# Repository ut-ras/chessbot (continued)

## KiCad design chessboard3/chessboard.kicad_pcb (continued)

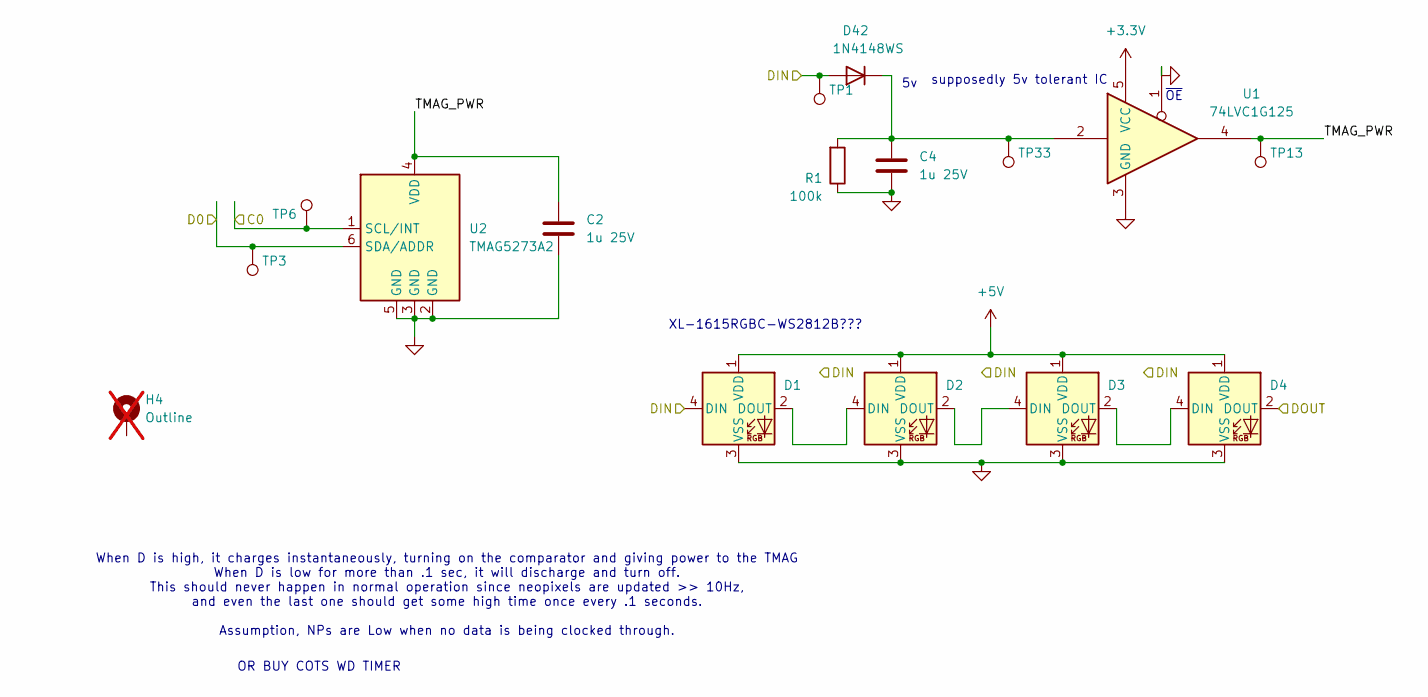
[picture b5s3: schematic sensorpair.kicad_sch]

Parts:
C2: 1u 25V; C_0402_1005Metric_Pad0.74x0.62mm_HandSolder
C4: 1u 25V; C_0402_1005Metric
D1, D2, D3, D4: XL-2121RGBC-WS2812B; SK6812-MINI-E-no-cut
D42: 1N4148WS; D_SOD-323_HandSoldering
H4: Outline; outline; not fitted
R1: 100k; R_0402_1005Metric_Pad0.72x0.64mm_HandSolder
TP1, TP3, TP6, TP13, TP33: TestPoint; TestPoint_THTPad_D1.0mm_Drill0.5mm
U1: 74LVC1G125; SOT-353_SC-70-5
U2: TMAG5273A2; SOT-23-6; LCSC C3715882

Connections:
+3.3V: U1.5 (VCC); also elsewhere on the board
+5V: D1.1 (VDD), D2.1 (VDD), D3.1 (VDD), D4.1 (VDD); also elsewhere on the board
/LED_IN: D1.4 (DIN), D42.2 (A), TP1.1; also elsewhere on the board
/Row0/sensorpair0/DOUT: D4.2 (DOUT); also elsewhere on the board
/Row0/sensorpair0/TMAG_PWR: C2.1, TP13.1, U1.4, U2.4 (VDD)
/SCL: TP6.1, U2.1 (SCL/INT); also elsewhere on the board
/SDA: TP3.1, U2.6 (SDA/ADDR); also elsewhere on the board
GND: C2.2, C4.2, D1.3 (VSS), D2.3 (VSS), D3.3 (VSS), D4.3 (VSS), R1.1, U1.1, U1.3 (GND), U2.2 (GND), U2.3 (GND), U2.5 (GND); also elsewhere on the board
unnamed: D1.2 (DOUT), D2.4 (DIN)
unnamed: D2.2 (DOUT), D3.4 (DIN)
unnamed: D3.2 (DOUT), D4.4 (DIN)
unnamed: C4.1, D42.1 (K), R1.2, TP33.1, U1.2

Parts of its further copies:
C6, C9, C11, C13, C15, C17, C19: 1u 25V; C_0402_1005Metric_Pad0.74x0.62mm_HandSolder
C7, C8, C10, C12, C14, C16, C18: 1u 25V; C_0402_1005Metric
D5, D6, D7, D8, D9, D10, D11, D12, D13, D14, D15, D16, D17, D18, D19, D20, D21, D22, D23, D24, D25, D26, D27, D28, D29, D30, D31, D32: XL-2121RGBC-WS2812B; SK6812-MINI-E-no-cut
D45, D48, D51, D54, D57, D60, D63: 1N4148WS; D_SOD-323_HandSoldering
H5, H6, H7, H8, H9, H10, H11: Outline; outline; not fitted
R9, R15, R21, R35, R37, R39, R41: 100k; R_0402_1005Metric_Pad0.72x0.64mm_HandSolder
TP2, TP4, TP5, TP7, TP8, TP9, TP10, TP11, TP12, TP14, TP15, TP16, TP17, TP18, TP19, TP20, TP21, TP22, TP23, TP24, TP25, TP26, TP27, TP28, TP29, TP30, TP31, TP32, TP34, TP35, TP36, TP37, TP38, TP39, TP40: TestPoint; TestPoint_THTPad_D1.0mm_Drill0.5mm
U3, U5, U7, U9, U13, U15, U17: TMAG5273A2; SOT-23-6; LCSC C3715882
U4, U6, U8, U11, U12, U14, U16: 74LVC1G125; SOT-353_SC-70-5

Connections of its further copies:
+3.3V: U4.5 (VCC), U6.5 (VCC), U8.5 (VCC), U11.5 (VCC), U12.5 (VCC), U14.5 (VCC), U16.5 (VCC); also elsewhere on the board
+5V: D5.1 (VDD), D6.1 (VDD), D7.1 (VDD), D8.1 (VDD), D9.1 (VDD), D10.1 (VDD), D11.1 (VDD), D12.1 (VDD), D13.1 (VDD), D14.1 (VDD), D15.1 (VDD), D16.1 (VDD), D17.1 (VDD), D18.1 (VDD), D19.1 (VDD), D20.1 (VDD), D21.1 (VDD), D22.1 (VDD), D23.1 (VDD), D24.1 (VDD), D25.1 (VDD), D26.1 (VDD), D27.1 (VDD), D28.1 (VDD), D29.1 (VDD), D30.1 (VDD), D31.1 (VDD), D32.1 (VDD); also elsewhere on the board
/LED_OUT: D32.2 (DOUT); also elsewhere on the board
/Row0/sensorpair0/DOUT: D5.4 (DIN), D45.2 (A), TP2.1; also elsewhere on the board
/Row0/sensorpair1/DOUT: D8.2 (DOUT), D9.4 (DIN), D48.2 (A), TP4.1
/Row0/sensorpair1/TMAG_PWR: C6.1, TP14.1, U3.4 (VDD), U4.4
/Row0/sensorpair2/DOUT: D12.2 (DOUT), D13.4 (DIN), D51.2 (A), TP5.1
/Row0/sensorpair2/TMAG_PWR: C9.1, TP16.1, U5.4 (VDD), U6.4
/Row0/sensorpair3/DOUT: D16.2 (DOUT), D17.4 (DIN), D54.2 (A), TP7.1
/Row0/sensorpair3/TMAG_PWR: C11.1, TP17.1, U7.4 (VDD), U8.4
/Row0/sensorpair4/DOUT: D20.2 (DOUT), D21.4 (DIN), D57.2 (A), TP8.1
/Row0/sensorpair4/TMAG_PWR: C13.1, TP19.1, U9.4 (VDD), U11.4
/Row0/sensorpair5/DOUT: D24.2 (DOUT), D25.4 (DIN), D60.2 (A), TP10.1
/Row0/sensorpair5/TMAG_PWR: C15.1, TP20.1, U12.4, U13.4 (VDD)
/Row0/sensorpair6/DOUT: D28.2 (DOUT), D29.4 (DIN), D63.2 (A), TP11.1
/Row0/sensorpair6/TMAG_PWR: C17.1, TP22.1, U14.4, U15.4 (VDD)
/Row0/sensorpair7/TMAG_PWR: C19.1, TP23.1, U16.4, U17.4 (VDD)
/SCL: TP12.1, TP18.1, TP24.1, TP26.1, TP28.1, TP30.1, TP32.1, U3.1 (SCL/INT), U5.1 (SCL/INT), U7.1 (SCL/INT), U9.1 (SCL/INT), U13.1 (SCL/INT), U15.1 (SCL/INT), U17.1 (SCL/INT); also elsewhere on the board
/SDA: TP9.1, TP15.1, TP21.1, TP25.1, TP27.1, TP29.1, TP31.1, U3.6 (SDA/ADDR), U5.6 (SDA/ADDR), U7.6 (SDA/ADDR), U9.6 (SDA/ADDR), U13.6 (SDA/ADDR), U15.6 (SDA/ADDR), U17.6 (SDA/ADDR); also elsewhere on the board
GND: C6.2, C7.2, C8.2, C9.2, C10.2, C11.2, C12.2, C13.2, C14.2, C15.2, C16.2, C17.2, C18.2, C19.2, D5.3 (VSS), D6.3 (VSS), D7.3 (VSS), D8.3 (VSS), D9.3 (VSS), D10.3 (VSS), D11.3 (VSS), D12.3 (VSS), D13.3 (VSS), D14.3 (VSS), D15.3 (VSS), D16.3 (VSS), D17.3 (VSS), D18.3 (VSS), D19.3 (VSS), D20.3 (VSS), D21.3 (VSS), D22.3 (VSS), D23.3 (VSS), D24.3 (VSS), D25.3 (VSS), D26.3 (VSS), D27.3 (VSS), D28.3 (VSS), D29.3 (VSS), D30.3 (VSS), D31.3 (VSS), D32.3 (VSS), R9.1, R15.1, R21.1, R35.1, R37.1, R39.1, R41.1, U3.2 (GND), U3.3 (GND), U3.5 (GND), U4.1, U4.3 (GND), U5.2 (GND), U5.3 (GND), U5.5 (GND), U6.1, U6.3 (GND), U7.2 (GND), U7.3 (GND), U7.5 (GND), U8.1, U8.3 (GND), U9.2 (GND), U9.3 (GND), U9.5 (GND), U11.1, U11.3 (GND), U12.1, U12.3 (GND), U13.2 (GND), U13.3 (GND), U13.5 (GND), U14.1, U14.3 (GND), U15.2 (GND), U15.3 (GND), U15.5 (GND), U16.1, U16.3 (GND), U17.2 (GND), U17.3 (GND), U17.5 (GND); also elsewhere on the board
unnamed: D5.2 (DOUT), D6.4 (DIN)
unnamed: D6.2 (DOUT), D7.4 (DIN)
unnamed: D7.2 (DOUT), D8.4 (DIN)
unnamed: D9.2 (DOUT), D10.4 (DIN)
unnamed: D10.2 (DOUT), D11.4 (DIN)
unnamed: D11.2 (DOUT), D12.4 (DIN)
unnamed: D13.2 (DOUT), D14.4 (DIN)
unnamed: D14.2 (DOUT), D15.4 (DIN)
unnamed: D15.2 (DOUT), D16.4 (DIN)
unnamed: D17.2 (DOUT), D18.4 (DIN)
unnamed: D18.2 (DOUT), D19.4 (DIN)
unnamed: D19.2 (DOUT), D20.4 (DIN)
unnamed: D21.2 (DOUT), D22.4 (DIN)
unnamed: D22.2 (DOUT), D23.4 (DIN)
unnamed: D23.2 (DOUT), D24.4 (DIN)
unnamed: D25.2 (DOUT), D26.4 (DIN)
unnamed: D26.2 (DOUT), D27.4 (DIN)
unnamed: D27.2 (DOUT), D28.4 (DIN)
unnamed: D29.2 (DOUT), D30.4 (DIN)
unnamed: D30.2 (DOUT), D31.4 (DIN)
unnamed: D31.2 (DOUT), D32.4 (DIN)
unnamed: C7.1, D45.1 (K), R9.2, TP34.1, U4.2
unnamed: C8.1, D48.1 (K), R15.2, TP35.1, U6.2
unnamed: C10.1, D51.1 (K), R21.2, TP36.1, U8.2
unnamed: C12.1, D54.1 (K), R35.2, TP37.1, U11.2
unnamed: C14.1, D57.1 (K), R37.2, TP38.1, U12.2
unnamed: C16.1, D60.1 (K), R39.2, TP39.1, U14.2
unnamed: C18.1, D63.1 (K), R41.2, TP40.1, U16.2

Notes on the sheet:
XL-1615RGBC-WS2812B???
~{OE}
OR BUY COTS WD TIMER
When D is high, it charges instantaneously, turning on the comparator and giving power to the TMAG When D is low for more than .1 sec, it will discharge and turn off. This should never happen in normal operation since neopixels are updated >> 10Hz, and even the last one should get some high time on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
supposedly 5v tolerant IC

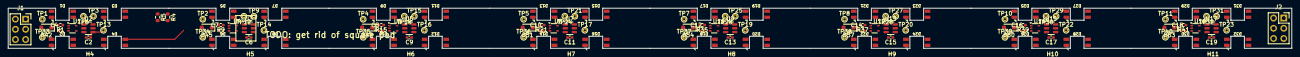
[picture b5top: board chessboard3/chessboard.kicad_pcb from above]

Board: 2 copper layers, 320.0 x 10.0 mm, 132 parts (0 on the bottom side), 54 nets.

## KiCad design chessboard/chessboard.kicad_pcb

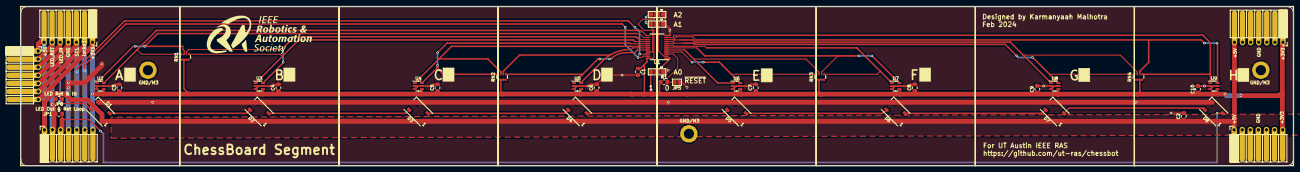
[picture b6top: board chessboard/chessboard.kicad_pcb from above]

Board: 2 copper layers, 400.0 x 50.0 mm, 46 parts (0 on the bottom side), 35 nets.

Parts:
C1, C3, C4, C5, C6, C7, C8, C9, C10: 100nF; C_0805_2012Metric_Pad1.18x1.45mm_HandSolder
C2: 22uF; C_0805_2012Metric_Pad1.18x1.45mm_HandSolder
D1, D2, D3, D4, D5, D6, D7, D8: XL-5050RGBC-WS2812B; LED_WS2812B_PLCC4_5.0x5.0mm_P3.2mm
H1, H2, H3: MountingHole_Pad; MountingHole_3.2mm_M3_ISO14580_Pad
J2, J3, J4, J5, J6: Conn_01x07; Custom PinSocket Edge Connector
JP1, JP6: SolderJumper_2_Open; R_0805_2012Metric_Pad1.20x1.40mm_HandSolder
JP2, JP3, JP4: SolderJumper_3_Open; SolderJumper-3_P2.0mm_Open_TrianglePad1.0x1.5mm
JP5: SolderJumper_2_Open; SolderJumper-2_P1.3mm_Open_Pad1.0x1.5mm
R1: 10k; R_0805_2012Metric_Pad1.20x1.40mm_HandSolder
RN1, RN2, RN3, RN4: 4.7k; R_Array_Convex_4x0603
U1: TCA9548APWR; TSSOP-24_4.4x7.8mm_P0.65mm
U2, U3, U4, U5, U6, U7, U8, U9: TMAG5273; SOT-23-6

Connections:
+3.3V: C1.1, C3.1, C4.1, C5.1, C6.1, C7.1, C8.1, C9.1, C10.1, J2.7, J3.1, J4.1, J5.7, J6.7, JP2.3 (B), JP3.3 (B), JP4.3 (B), R1.1, RN1.1 (R1.1), RN1.2 (R2.1), RN1.3 (R3.1), RN1.4 (R4.1), RN2.1 (R1.1), RN2.2 (R2.1), RN2.3 (R3.1), RN2.4 (R4.1), RN3.1 (R1.1), RN3.2 (R2.1), RN3.3 (R3.1), RN3.4 (R4.1), RN4.1 (R1.1), RN4.2 (R2.1), RN4.3 (R3.1), RN4.4 (R4.1), U1.24 (VCC), U2.4 (VDD), U3.4 (VDD), U4.4 (VDD), U5.4 (VDD), U6.4 (VDD), U7.4 (VDD), U8.4 (VDD), U9.4 (VDD)
+5V: C2.1, D1.1 (VDD), D2.1 (VDD), D3.1 (VDD), D4.1 (VDD), D5.1 (VDD), D6.1 (VDD), D7.1 (VDD), D8.1 (VDD), J2.1, J3.7, J4.7, J5.1, J6.1
/LED_IN: D1.4 (DIN), J3.5, J6.3, JP6.1 (A)
/LED_OUT: D8.2 (DOUT), J2.3, JP1.1 (A)
/LED_RET: J2.2, J3.6, J6.2, JP1.2 (B), JP6.2 (B)
/Row0/sensorpair0/C0: RN3.7 (R2.2), U1.5 (SC0), U6.1 (SCL/INT)
/Row0/sensorpair0/C1: RN3.5 (R4.2), U1.7 (SC1), U7.1 (SCL/INT)
/Row0/sensorpair0/D0: RN3.8 (R1.2), U1.4 (SD0), U6.6 (SDA/ADDR)
/Row0/sensorpair0/D1: RN3.6 (R3.2), U1.6 (SD1), U7.6 (SDA/ADDR)
/Row0/sensorpair1/C0: RN4.7 (R2.2), U1.9 (SC2), U8.1 (SCL/INT)
/Row0/sensorpair1/C1: RN4.5 (R4.2), U1.11 (SC3), U9.1 (SCL/INT)
/Row0/sensorpair1/D0: RN4.8 (R1.2), U1.8 (SD2), U8.6 (SDA/ADDR)
/Row0/sensorpair1/D1: RN4.6 (R3.2), U1.10 (SD3), U9.6 (SDA/ADDR)
/Row0/sensorpair2/C0: RN2.7 (R2.2), U1.18 (SC6), U4.1 (SCL/INT)
/Row0/sensorpair2/C1: RN2.5 (R4.2), U1.20 (SC7), U5.1 (SCL/INT)
/Row0/sensorpair2/D0: RN2.8 (R1.2), U1.17 (SD6), U4.6 (SDA/ADDR)
/Row0/sensorpair2/D1: RN2.6 (R3.2), U1.19 (SD7), U5.6 (SDA/ADDR)
/Row0/sensorpair3/C0: RN1.7 (R2.2), U1.14 (SC4), U2.1 (SCL/INT)
/Row0/sensorpair3/C1: RN1.5 (R4.2), U1.16 (SC5), U3.1 (SCL/INT)
/Row0/sensorpair3/D0: RN1.8 (R1.2), U1.13 (SD4), U2.6 (SDA/ADDR)
/Row0/sensorpair3/D1: RN1.6 (R3.2), U1.15 (SD5), U3.6 (SDA/ADDR)
/SCL: J2.5, J3.3, J6.5, U1.22 (SCL)
/SDA: J2.6, J3.2, J6.6, U1.23 (SDA)
GND: C1.2, C2.2, C3.2, C4.2, C5.2, C6.2, C7.2, C8.2, C9.2, C10.2, D1.3 (VSS), D2.3 (VSS), D3.3 (VSS), D4.3 (VSS), D5.3 (VSS), D6.3 (VSS), D7.3 (VSS), D8.3 (VSS), H1.1, H2.1, H3.1, J2.4, J3.4, J4.4, J5.4, J6.4, JP2.1 (A), JP3.1 (A), JP4.1 (A), JP5.1 (A), U1.12 (GND), U2.2 (GND), U2.3 (GND), U2.5 (GND), U3.2 (GND), U3.3 (GND), U3.5 (GND), U4.2 (GND), U4.3 (GND), U4.5 (GND), U5.2 (GND), U5.3 (GND), U5.5 (GND), U6.2 (GND), U6.3 (GND), U6.5 (GND), U7.2 (GND), U7.3 (GND), U7.5 (GND), U8.2 (GND), U8.3 (GND), U8.5 (GND), U9.2 (GND), U9.3 (GND), U9.5 (GND)
unnamed: D1.2 (DOUT), D2.4 (DIN)
unnamed: D2.2 (DOUT), D3.4 (DIN)
unnamed: D3.2 (DOUT), D4.4 (DIN)
unnamed: D4.2 (DOUT), D5.4 (DIN)
unnamed: D5.2 (DOUT), D6.4 (DIN)
unnamed: D6.2 (DOUT), D7.4 (DIN)
unnamed: D7.2 (DOUT), D8.4 (DIN)
unnamed: JP2.2 (C), U1.2 (A1)
unnamed: JP3.2 (C), U1.21 (A2)
unnamed: JP4.2 (C), U1.1 (A0)
unnamed: JP5.2 (B), R1.2, U1.3 (~RESET)

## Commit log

2024-01-20 lay out chess board sensors + leds
2024-01-21 add some power logic, split chessboard and control board
2024-02-01 new single row board
2024-02-06 make it pretty
2024-02-06 ready to buy
2024-02-06 ok good now forreal
2024-02-08 Testing Bitboard analysis in python
2024-02-08 modified: python/bitboard_move_analysis_test.py
2024-02-08 some docs on Bitboard testing code
2024-02-08 Bitboard analysis somewhat working, using xor on the two bitboards to get changes between
2024-02-08 Works, only testing first move against default board so far
2024-02-08 cleaned up slightly, need to fix validity check as well
2024-02-08 Added Loop
2024-02-13 Added SRAMP firmware to Repo
2024-02-13 Changes to be committed: deleted: cplusplus/platformio/Chessbot_Arduino_Testing/.gitignore deleted: cplusplus/platformio/Chessbot_Arduino_Testing/.vscode/extensions.json deleted: cplusplus/platformio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
2024-02-13 Moved SRAMP firmware into PlatformIO project
2024-02-13 modified: cplusplus/platformio/Chessbot_SRAMP/include/config.h modified: cplusplus/platformio/Chessbot_SRAMP/platformio.ini
2024-02-15 nearly everything should be pretty and reading and processing
2024-02-15 define API and do some sensor stuff
2024-02-15 implement sensorarray and magvals
2024-02-15 implemented crc checking, and basic tests for it, now I really need to sleep and do homework tmrw forreal
2024-02-20 new file: bitboard_with_stockfish.py
2024-02-20 dumdum i2c
2024-02-20 modified: .gitignore
2024-03-11 Display output and Move Legality Testing
2024-03-11 new file: 6px_Icons/AGoblinAppears-o2aV.ttf modified: chess_board_simulation.png modified: python/bitboard_with_stockfish.py modified: python/display_output.py
2024-03-11 deleted: python/pilfont.py
2024-03-11 new file: 6px_Icons/FFFFORWA.TTF new file: 6px_Icons/m3x6.ttf new file: 6px_Icons/m5x7.ttf modified: chess_board_simulation.png modified: python/bitboard_with_stockfish.py modified: python/display_ou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
2024-03-11 Castling mostly working, automatic tester working
2024-03-16 more bug fixes
2024-03-16 removed old files
2024-03-16 minor error fix
2024-03-16 modified: chess_board_simulation.png modified: python/bitboard_with_stockfish.py
2024-03-17 rename icons folder, added requirements.txt
2024-03-17 Added stockfish diffficulty selection, fixed some check detection issues, still have castling issues
2024-03-18 added some starting code for the stepper movement integration
2024-03-25 modified: .gitignore modified: README.md modified: python/bitboard_with_stockfish.py
2024-04-10 Can stream moves of a user's current game
2024-04-22 idk sorry
2024-04-23 adding mqtt -Zaara/Olyvia
2024-04-23 streams game moves yay
2024-05-11 movement from lichess works (by ashley zaara olyvia) !!!
2024-05-11 led write from mqtt
2024-05-11 demo with magnets lighting up the LEDs near them
2024-05-11 requirements
2024-05-11 gitignore update
2024-05-11 gitignore updated to exclude bin/ , requirements updated
2024-05-12 perfomance, debuggin, hardware tester
2024-05-12 negligible magnetometer stuff
2024-05-14 updates to controlboard
2024-05-14 to not shit git
2024-05-14 Added HighLevelDiagram.drawio
2024-05-14 path_tester good
2024-05-14 Added HighLevelDiagram.drawio.html
2024-05-14 Added HighLevelDiagram.drawio.png
2024-05-16 path planning
2024-05-16 Added path_planner.py and modified path_tester.p
2024-05-16 added basic path planner
2024-05-16 fixed path to work with rook
2024-05-20 boilerplate for a QT python gui
2024-05-20 Control Board major progress
2024-05-20 remove USB
2024-05-21 boardstate tester added and fixed path
2024-05-21 just added file and folder
2024-05-23 board state work in progress
2024-05-23 last change to tester
2024-05-25 bad naming on my part
2024-05-25 more progress on controlboard pcb
2024-05-25 Setup for new pi
2024-05-25 huge changes for magnetometer reader performance
2024-05-25 make i2c faster
2024-05-25 better values in magnet_to_led visualizer
2024-05-25 Fix magnet recordings to 64 squares (dummy data) and rename
2024-05-25 switch to 2 val /path
2024-05-25 niceify tester
2024-05-25 dum bug in magnet_to_led merge
2024-05-27 ControlBoard Schematic nearly done
2024-05-28 tester is back to working!!
2024-05-28 disable prints
2024-05-28 show /robotmoves and /playermoves as text in tester
2024-05-28 schematic improvements
2024-05-28 improve pinout
2024-05-28 improvements
2024-05-28 erc should be good now
2024-05-29 pcb layout work
2024-06-01 progress
2024-06-01 yay its all connected
2024-06-03 controlboard: fix critical mosfet errors
2024-06-03 remove production file
2024-06-04 nice silkscreen stuff
2024-06-04 update pcb easter egg
2024-06-05 vectors on tester, boardstate
2024-06-06 simplified requirements.txt, added stockfish to pi_config
2024-06-12 controlboard finalized and ordered!!!
2024-06-14 tester: render_vectors changes for visibility
2024-06-14 magnetometer: remove disabled squares; account for TMAGA1 chip in one square
2024-06-14 change led behavior slightly
2024-06-14 significantly improve led output perfomance
2024-07-01 MAKE IT WORK!!!!!!!!!!!!!!!!!!
2024-07-08 Linux: restart services on fail
2024-07-08 python/stepper: more dynamic fast timings
2024-07-08 Path Planner: home on invalid move
2024-07-08 magnet_to_bitboard_boardstate.py added
2024-07-08 Linux: bitboard service
2024-07-08 Add stockfish mqtt response
2024-07-08 python/path_planner: flip rows properly
2024-07-08 make tester work better
2024-07-08 tester
2024-07-09 Very basic player move and stockfish response (no captures yet)
    new file: python/.gitignore
    modified: python/bitboard.py
    modified: python/bitboard_with_stockfish.py
    new file: python/board_analyzer.py
    deleted: python/magnet_to_bitboard_boardstate.py
    new file: python/realboard.py
2024-07-09 aaaaaa
2024-07-29 diagnol pathing
2024-09-16 chessboardv3
2024-10-07 nothing new
2024-11-12 We fixed the tester i.e. work-er
2024-11-19 chessboard5
2024-11-19 Control board changes
    Made a few control board changes (green checks on discord)
2024-12-03 update slightly
2025-01-03 fix up schematic for chessboard5
2025-01-03 Progress!!!
2025-01-04 pcb progress 2
2025-01-04 finished chessboard v5!!!
2025-01-09 fix chessboard5 for ordering;
2025-02-04 "pillow version update"
2025-03-05 arduino tester
2025-04-01 corexy + other random shit from idk when tbh
2025-04-09 rwbg leds
2025-04-09 leds fixed
2025-04-13 make stepper wokr
2025-04-13 make led work
2025-04-13 fixed magnetometer ordering issues
2025-04-14 movement to size
2025-04-14 tester size fix
2025-04-14 path planner
2025-04-14 stepper directions not flipped anymore yay
2025-04-14 testing step size
2025-04-14 tester scale
2025-10-01 clean up repo
2025-10-01 Remove .DS_Store and add to .gitignore
2025-10-01 deleteeee
2025-10-02 Revert controlboard to June 12th 2024
2025-10-02 make linux stuff work on new repo structure + new pi
2025-10-22 fix read_mag
